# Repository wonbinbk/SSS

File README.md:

SMART SOLDERING PROJECT

1. Introduction
- I want to make a smart soldering station that could do something smart-ish.
- I follow a project on istyle.kr of a Korean hobby. He was using an AVR and
coding in ASM.
- I use PIC microcontroller instead because I am familiar with PIC micro.
Maybe in the future I will port this project into a STM, because STM microcontrollers
are know for its low price.

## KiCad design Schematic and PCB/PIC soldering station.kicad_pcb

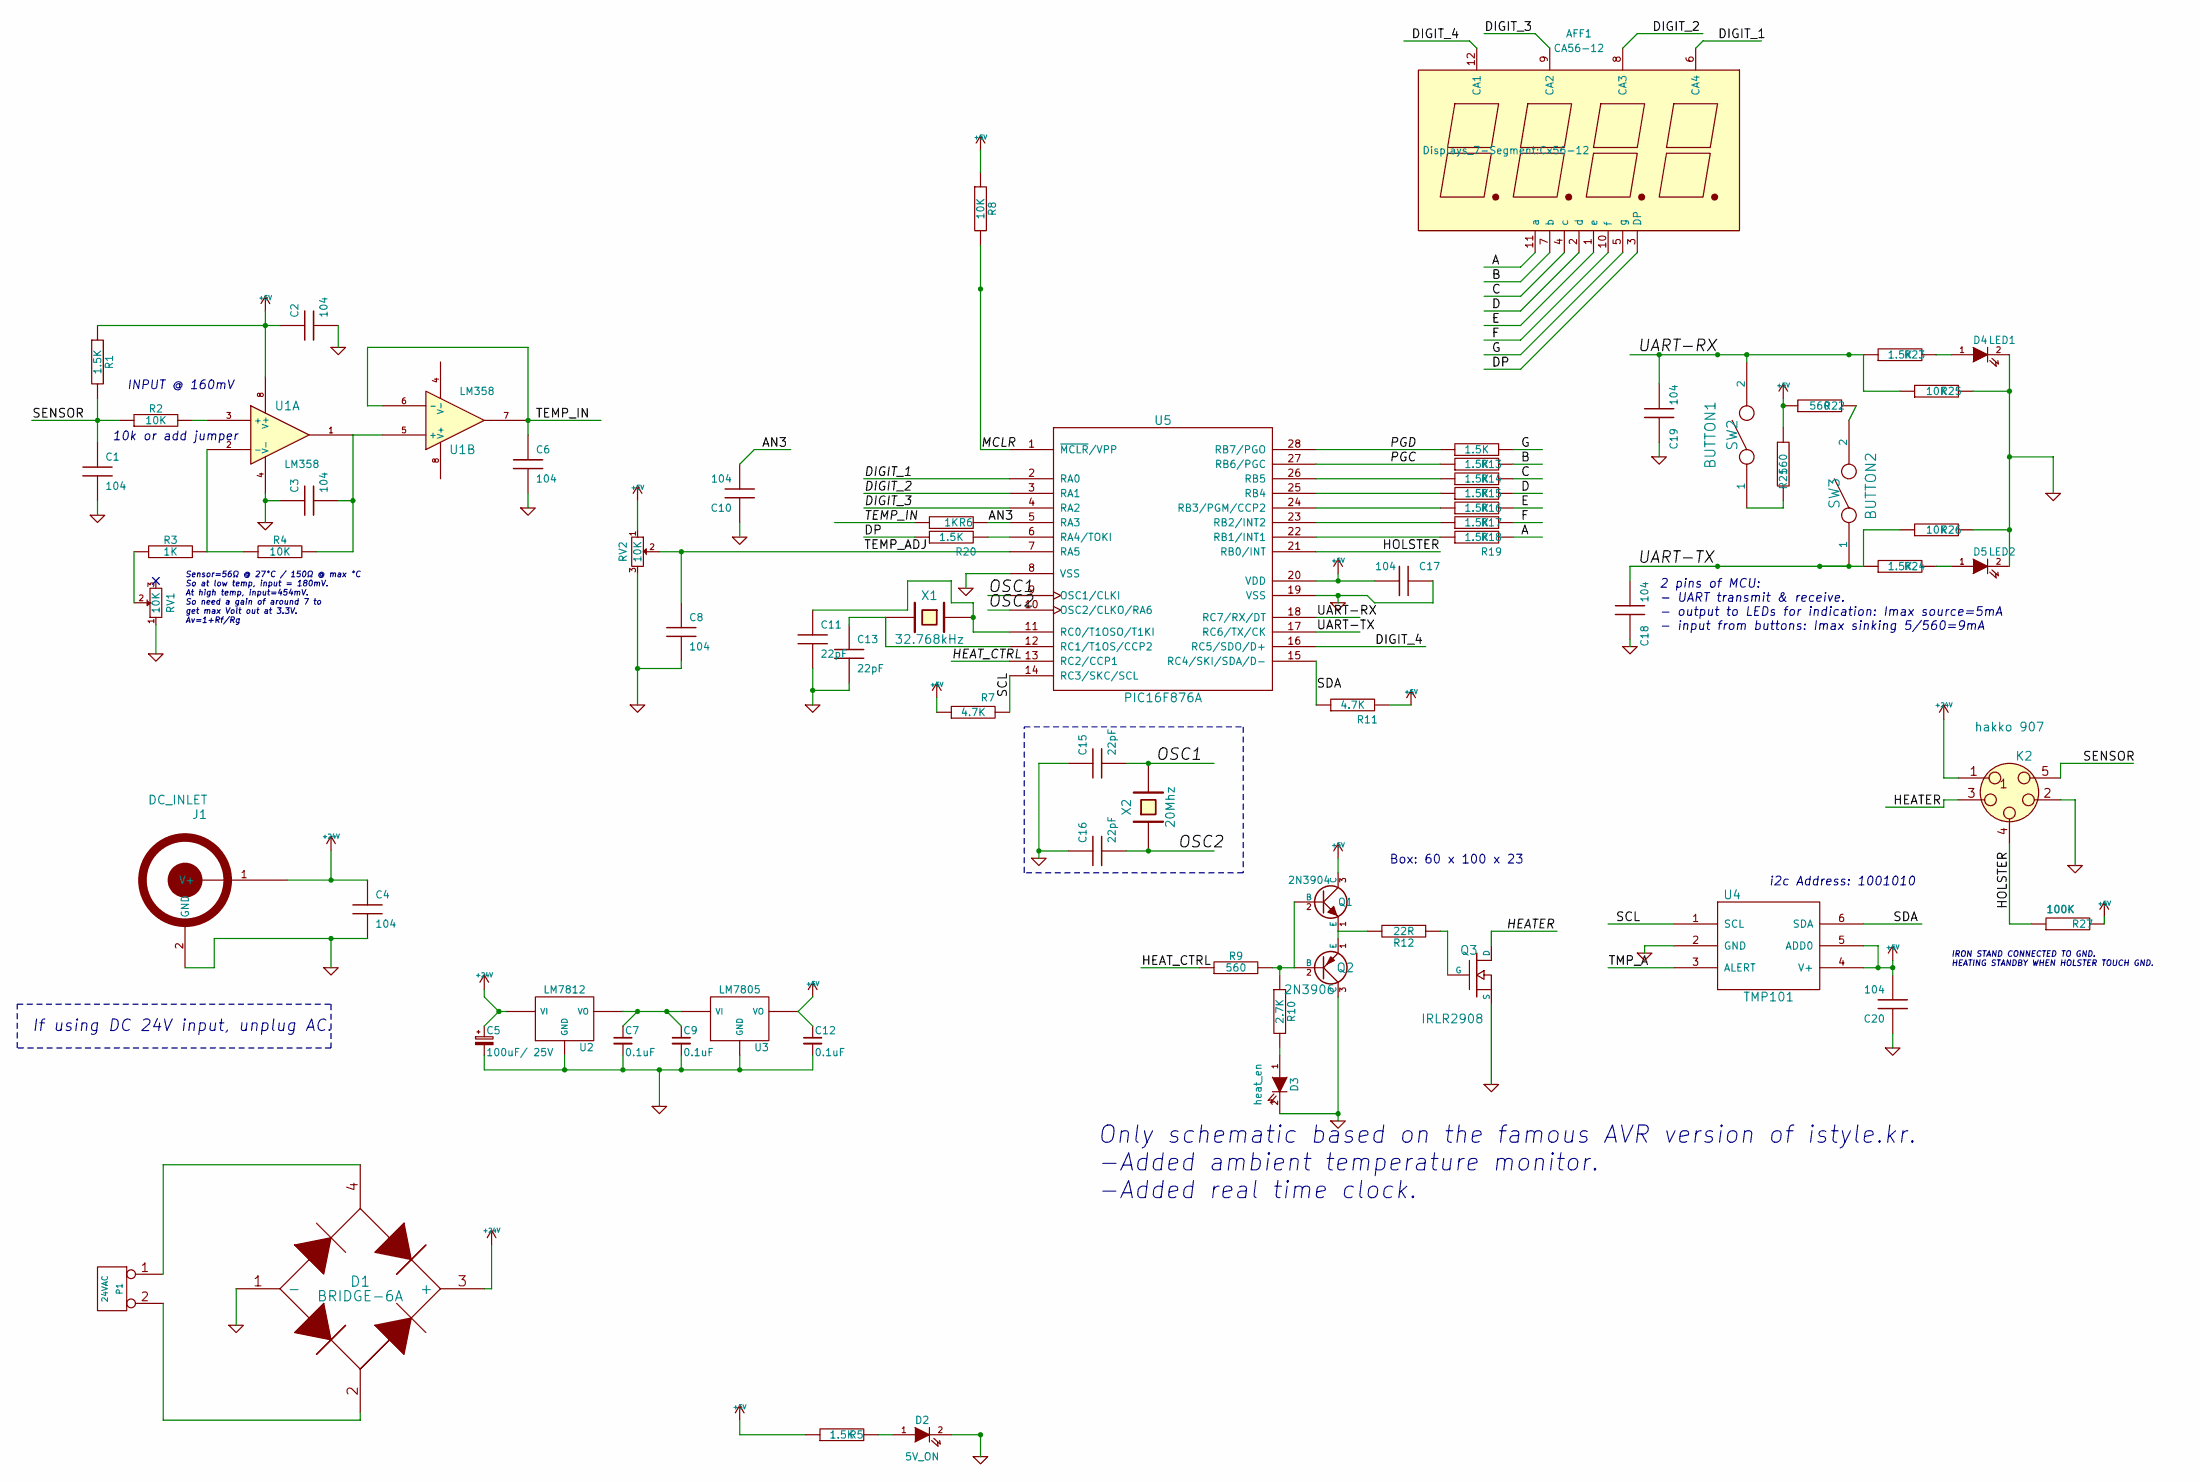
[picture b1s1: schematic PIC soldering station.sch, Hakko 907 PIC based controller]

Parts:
AFF1: CA56-12; Cx56-12
C1, C2, C3, C4, C6, C8, C10, C17, C18, C19, C20: 104; cnp_3mm_disc
C5: 100uF/ 25V; CP_6.3x11mm
C7, C9, C12: 0.1uF; cnp_3mm_disc
C11, C13, C15, C16: 22pF; cnp_3mm_disc
D1: BRIDGE-6A; Diode_bridge_KPBC60xx
D2: 5V_ON; LED-3MM
D3: heat_en; LED-3MM
D4: LED1; LED-3MM
D5: LED2; LED-3MM
J1: DC_INLET; dc_socket
K2: hakko 907; mors_5p
P1: 24VAC; TerminalBlock_Pheonix_MKDS1.5-2pol
Q1: 2N3904; TO-92_Molded_Wide_Oval
Q2: 2N3906; TO-92_Molded_Wide_Oval
Q3: IRLR2908; DPAK-3_GDS
R1, R5, R13, R14, R15, R16, R17, R18, R19, R20, R23, R24: 1.5K; R3
R2, R4, R8, R25, R26: 10K; R3
R3, R6: 1K; R3
R7, R11: 4.7K; R3
R9, R21, R22: 560; R3
R10: 2.7K; R3
R12: 22R; R3
R27: 100K; R3
RV1, RV2: 10K; SW_SPST_B3S-1100
SW2: BUTTON1; SW_PUSH_SMALL
SW3: BUTTON2; SW_PUSH_SMALL
U1: LM358; SOIC-8-N
U2: LM7812; TO-220_Neutral123_Vertical_LargePads
U3: LM7805; TO-220_Neutral123_Vertical_LargePads
U4: TMP101; SOT-23-6
U5: PIC16F876A; DIP-28_W7.62mm_LongPads
X1: 32.768kHz; Crystal_Round_Horizontal_3mm_BigPad
X2: 20Mhz; Crystal_HC50-U_Vertical

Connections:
+5V: C2.1, C12.1, C17.2, C20.2, Q1.3 (C), R1.1, R5.1, R7.1, R8.1, R11.2, R21.1, R22.1, R27.2, RV2.1, U1.8 (V+), U3.3 (VO), U4.4 (V+), U4.5 (ADD0), U5.20 (VDD)
+24V: C4.1, C5.1, D1.3 (+), J1.1 (V+), K2.1, U2.1 (VI)
/A: AFF1.11 (a), R19.2
/AN3: C10.2, R6.2, U5.5 (RA3)
/B: AFF1.7 (b), R14.2
/C: AFF1.4 (c), R15.2
/D: AFF1.2 (d), R16.2
/DIGIT_1: AFF1.6 (CA4), U5.2 (RA0)
/DIGIT_2: AFF1.8 (CA3), U5.3 (RA1)
/DIGIT_3: AFF1.9 (CA2), U5.4 (RA2)
/DIGIT_4: AFF1.12 (CA1), U5.16 (RC5/SDO/D+)
/DP: AFF1.3 (DP), R20.1
/E: AFF1.1 (e), R17.2
/F: AFF1.10 (f), R18.2
/G: AFF1.5 (g), R13.2
/HEATER: K2.3 (P2), Q3.D
/HEAT_CTRL: R9.1, U5.13 (RC2/CCP1)
/HOLSTER: K2.4 (P3), R27.1, U5.21 (RB0/INT)
/MCLR: R8.2, U5.1 (~MCLR~/VPP)
/OSC1: C15.2, U5.9 (OSC1/CLKI), X2.2
/OSC2: C16.2, U5.10 (OSC2/CLKO/RA6), X2.1
/PGC: R14.1, U5.27 (RB6/PGC)
/PGD: R13.1, U5.28 (RB7/PGO)
/SCL: R7.2, U4.1 (SCL), U5.14 (RC3/SKC/SCL)
/SDA: R11.1, U4.6 (SDA), U5.15 (RC4/SKI/SDA/D-)
/SENSOR: C1.1, K2.5, R1.2, R2.1
/TEMP_ADJ: C8.1, RV2.2, U5.7 (RA5)
/TEMP_IN: C6.1, R6.1, U1.6 (-), U1.7
/TMP_A: U4.3 (ALERT)
/UART-RX: C19.2, R23.1, R25.1, SW2.2, U5.18 (RC7/RX/DT)
/UART-TX: C18.2, R24.1, R26.1, SW3.1, U5.17 (RC6/TX/CK)
GND: C1.2, C2.2, C3.1, C4.2, C5.2, C6.2, C7.2, C8.2, C9.2, C10.1, C11.2, C12.2, C13.2, C15.1, C16.1, C17.1, C18.1, C19.1, C20.1, D1.1 (-), D2.2 (K), D3.2 (K), D4.2 (K), D5.2 (K), J1.2 (GND), K2.2 (P3), Q2.3 (C), Q3.S, R25.2, R26.2, RV1.1, RV2.3, U1.4 (V-), U2.2 (GND), U3.2 (GND), U4.2 (GND), U5.8 (VSS), U5.19 (VSS)
unnamed: C3.2, R4.2, U1.1, U1.5 (+)
unnamed: C7.1, C9.1, U2.3 (VO), U3.1 (VI)
unnamed: C11.1, U5.11 (RC0/T1OSO/T1KI), X1.1
unnamed: C13.1, U5.12 (RC1/T1OS/CCP2), X1.2
unnamed: D1.2, P1.2 (PM)
unnamed: D1.4, P1.1
unnamed: D2.1 (A), R5.2
unnamed: D3.1 (A), R10.2
unnamed: D4.1 (A), R23.2
unnamed: D5.1 (A), R24.2
unnamed: Q1.1 (E), Q2.1 (E), R12.2
unnamed: Q1.2 (B), Q2.2 (B), R9.2, R10.1
unnamed: Q3.G, R12.1
unnamed: R2.2, U1.3 (+)
unnamed: R3.1, RV1.2
unnamed: R3.2, R4.1, U1.2 (-)
unnamed: R15.1, U5.26 (RB5)
unnamed: R16.1, U5.25 (RB4)
unnamed: R17.1, U5.24 (RB3/PGM/CCP2)
unnamed: R18.1, U5.23 (RB2/INT2)
unnamed: R19.1, U5.22 (RB1/INT1)
unnamed: R20.2, U5.6 (RA4/TOKI)
unnamed: R21.2, SW2.1
unnamed: R22.2, SW3.2

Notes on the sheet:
INPUT @ 160mV
Sensor=56Ω @ 27°C / 150Ω @ max °C So at low temp, input = 180mV. At high temp, input=454mV. So need a gain of around 7 to get max Volt out at 3.3V. Av=1+Rf/Rg
10k or add jumper
i2c Address: 1001010
Only schematic based on the famous AVR version of istyle.kr. -Added ambient temperature monitor. -Added real time clock.
If using DC 24V input, unplug AC.
Box: 60 x 100 x 23
2 pins of MCU: - UART transmit & receive. - output to LEDs for indication: Imax source=5mA - input from buttons: Imax sinking 5/560=9mA
IRON STAND CONNECTED TO GND. HEATING STANDBY WHEN HOLSTER TOUCH GND.

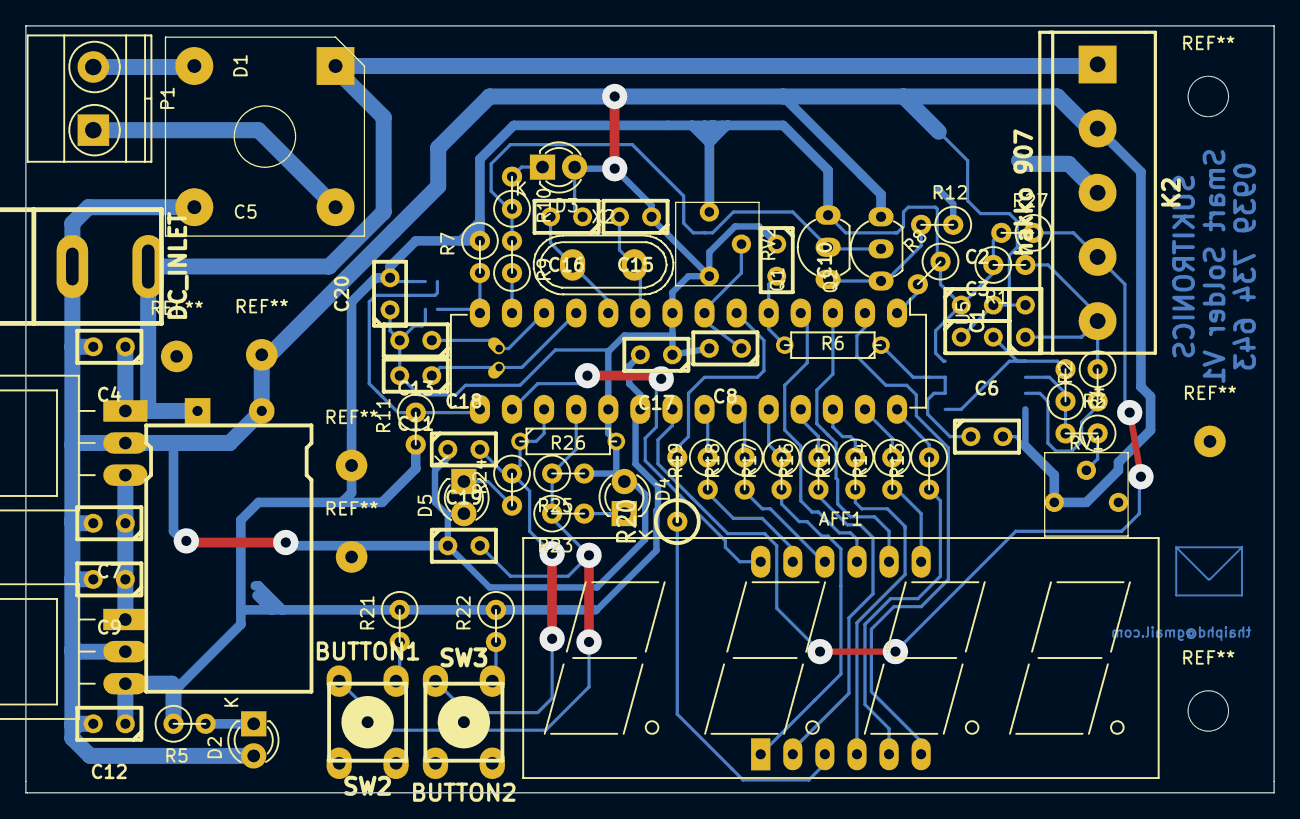
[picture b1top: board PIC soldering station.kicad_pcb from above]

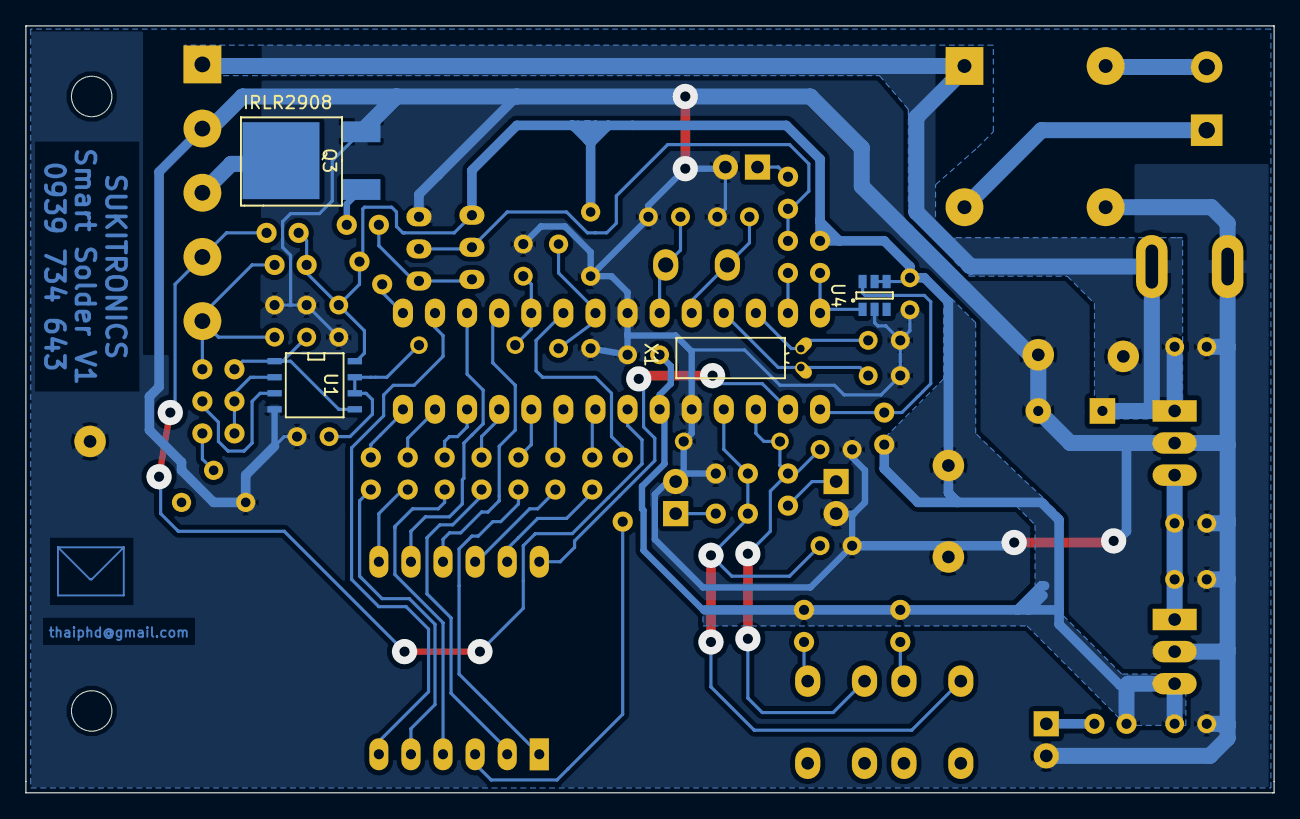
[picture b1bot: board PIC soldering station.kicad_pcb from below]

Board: 2 copper layers, 98.8 x 60.7 mm, 69 parts (4 on the bottom side), 55 nets.

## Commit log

2016-04-18 initial project version 1
2016-04-18 Added main.hex
2016-04-20 Todo: why the target voltage read wrong?
2016-04-20 Just add a spreadsheet for easy getting value for 7 segment data port
2016-04-20 Working. Fixed adc reading problem: add 30us delay after switching to another channel (to properly charge C_HOLD).
2016-04-20 Add schematic and PCB
2016-04-21 Nothing
2016-04-21 Add clock while in standby mode (ie,iron on holster)
2016-04-24 Added time adjusting function
2016-07-17 Version 1.1: Working OK without PID
2016-07-19 Version 3: With Proportional control only
2016-07-24 Added auto-standby and auto-poweroff; calibration mode
2016-08-02 - Clean up code. Make comments more meaningful... - Add PID tuning data.
2018-04-19 Add file via upload
    Fix the plotted via on PIC pin 6.
